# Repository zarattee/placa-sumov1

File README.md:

# placa-sumov1
 placa controladora para robot sumo, esta placa esta usando como microcontrolador un arduino nano

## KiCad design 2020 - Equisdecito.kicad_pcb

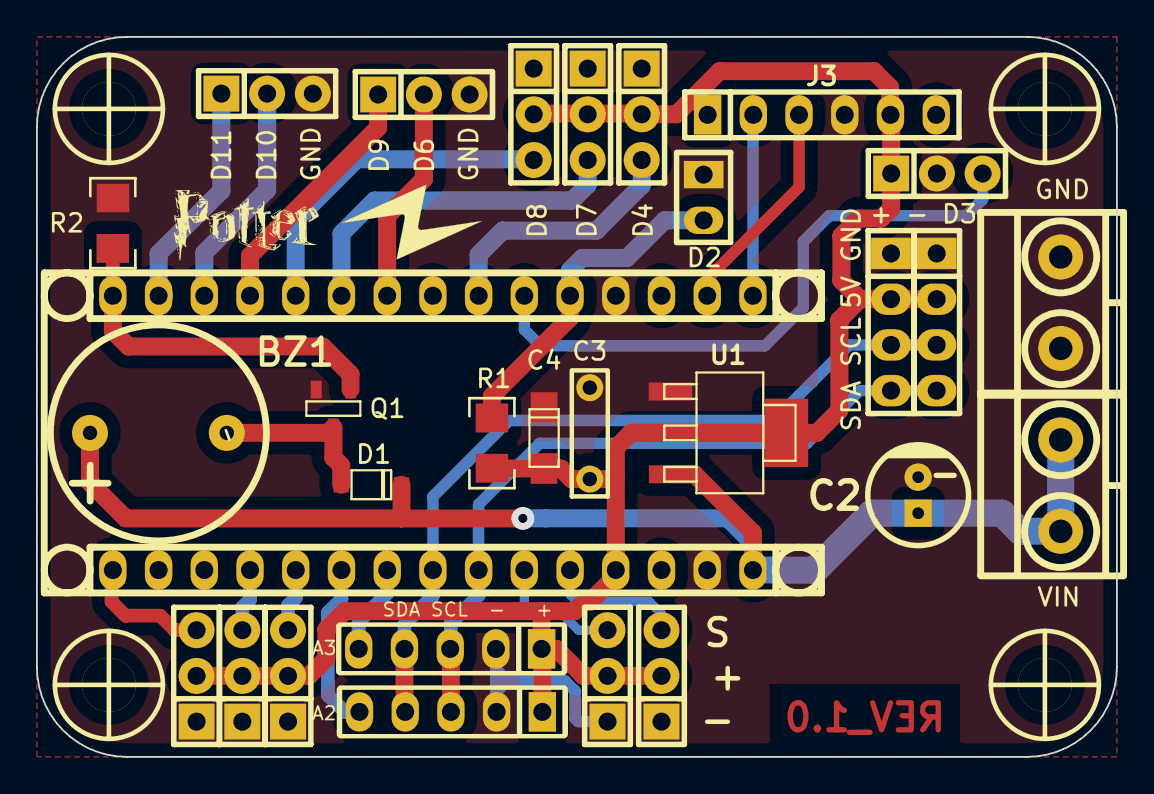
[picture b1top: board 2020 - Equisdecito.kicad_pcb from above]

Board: 2 copper layers, 60.0 x 40.0 mm, 35 parts (0 on the bottom side), 25 nets.

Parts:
BZ1: Buzzer; Buzzer_12mm
C2: 100uF; CAP_ELEC_5x11mm
C3: 100nF; CAP_0.2
C4: 10uF; CAP_TAN_A
D1: DIODE; sod123
H1, H2, H3, H4: Mounting_Hole; hole_3mm
J1: VL53L0x_IZQ; Pin_Strip_5
J2: VL53L0x_DER; Pin_Strip_5
J3: HC-05
J4: Pantalla Oled; pin_strip_4
J5: Batería (+); BORNERA2_AZUL
J6: sharp1; Pin_Strip_3
J7: tatami 1; Pin_Strip_3
J8: tatami 2; Pin_Strip_3
J9: Aux1; Pin_Strip_3
J10: IMU; pin_strip_4
J11: Batería (-); BORNERA2_AZUL
J12, J13, J15, J17: sharp2; Pin_Strip_3
J14: Arduino_Nano_Header; arduino_nano_header_Sumo
J16: MOTOR 1; Pin_Strip_3
J18: MOTOR 2; Pin_Strip_3
J19: AUX6; Pin_Strip_3
LG1: Mounting_Hole; Logo_Rayo
LG3: Mounting_Hole; Logo_potter
Q1: 2N7002; SOT23
R1: 10K; R_1206
R2: 10k; R_1206
SW1: Pulsador; Pin_strip_2
U1: LM1117-SOT; SOT223

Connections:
+5V: C3.1, C4.1, J1.1, J2.1, J3.5, J4.2, J6.2, J7.2, J8.2, J9.1, J10.2, J12.2, J13.2, J14.27, J15.2, J17.2, J19.2, R1.1, U1.2, U1.4
/AUX1: J9.3, J14.6
/AUX2: J14.15, Q1.1, R2.1
/AUX3: J14.11, J17.3
/AUX4: J14.10, J15.3
/AUX5: J12.3, J14.7
/AUX6: J14.16, J19.3
/DISTANCIA_D: J13.3, J14.19
/DISTANCIA_I: J6.3, J14.20
/M1A: J14.12, J16.1
/M1B: J14.9, J16.2
/M2A: J14.14, J18.1
/M2B: J14.13, J18.2
/Rx: J3.3, J14.2
/S1: J1.5, J14.22
/S2: J2.5, J14.21
/SCL: J1.3, J2.3, J4.4, J10.4, J14.24
/SDA: J1.4, J2.4, J4.3, J10.3, J14.23
/START: J14.5, R1.2, SW1.2
/TATAMI_FD: J7.3, J14.25
/TATAMI_FI: J8.3, J14.26
/Tx: J3.2, J14.1
/Vin: BZ1.1, C2.1, D1.2, J5.1, J5.2, J14.30, U1.3
GND: C2.2, C3.2, C4.2, J1.2, J2.2, J3.4, J4.1, J6.1, J7.1, J8.1, J9.2, J10.1, J11.1, J11.2, J12.1, J13.1, J14.4, J14.29, J15.1, J16.3, J17.1, J18.3, J19.1, Q1.3, R2.2, SW1.1, U1.1
unnamed: BZ1.2, D1.1, Q1.2

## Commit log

2020-10-22 se agregaron los gerbers
    se agregaron los archivos de fabricacion
2020-11-04 BOM & ToDo list
    * Generé la lista de materiales interactiva para el montaje del proyecto
    * Agregué un archivo con la lista de tareas pendientes
2021-01-07 Actualizaciones varias
    Generé el sch en PDF
    Corregi las dimensiones a numero redondo
    Actualice el ToDo.txt
2021-01-08 MODIFICACIONES
    se quito un logo en la capa bottom,se agrego descripción en el sch, y por ultimo se agrego revisión
